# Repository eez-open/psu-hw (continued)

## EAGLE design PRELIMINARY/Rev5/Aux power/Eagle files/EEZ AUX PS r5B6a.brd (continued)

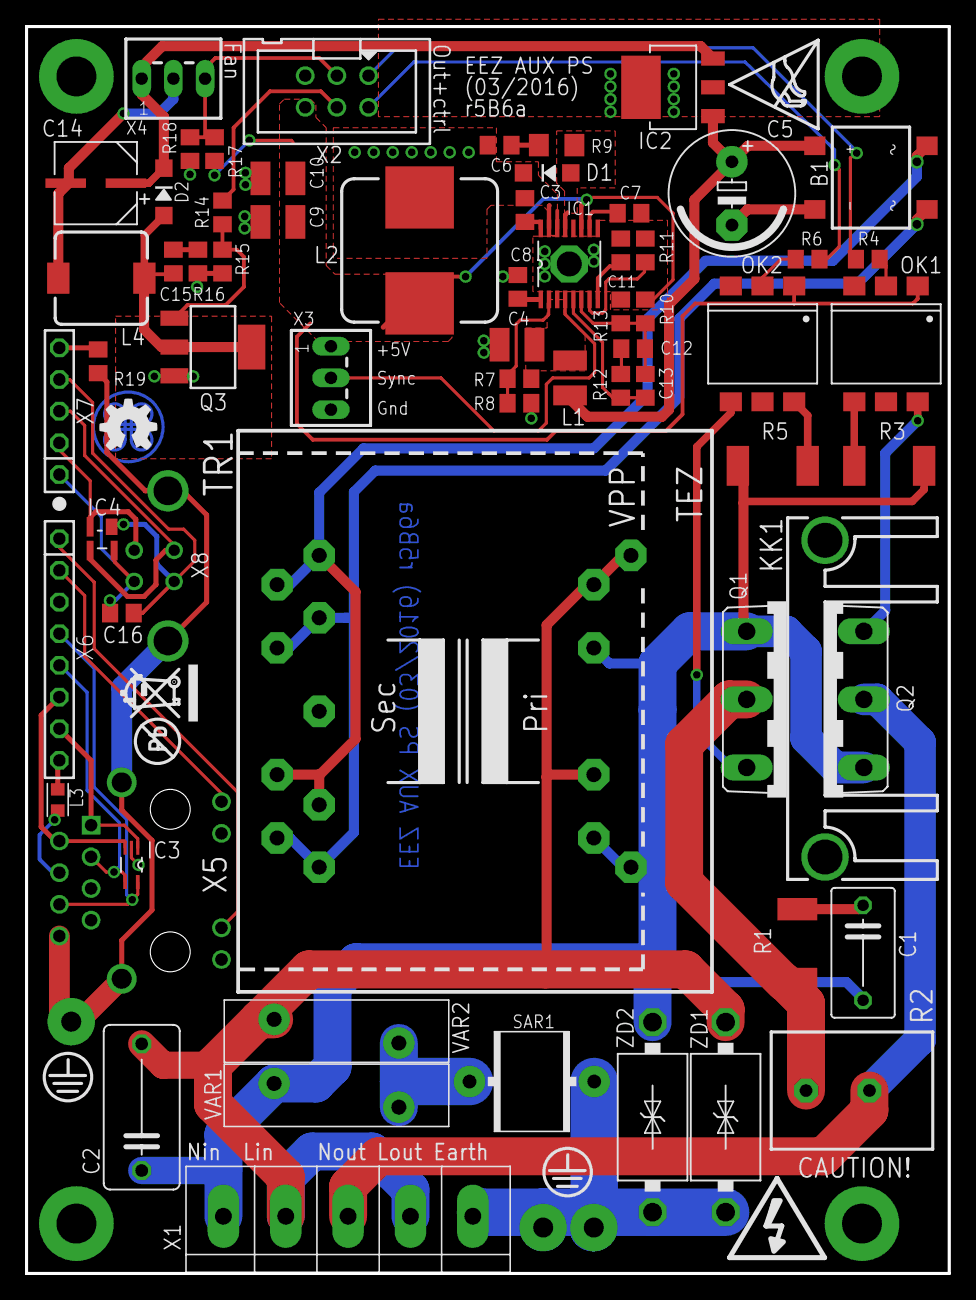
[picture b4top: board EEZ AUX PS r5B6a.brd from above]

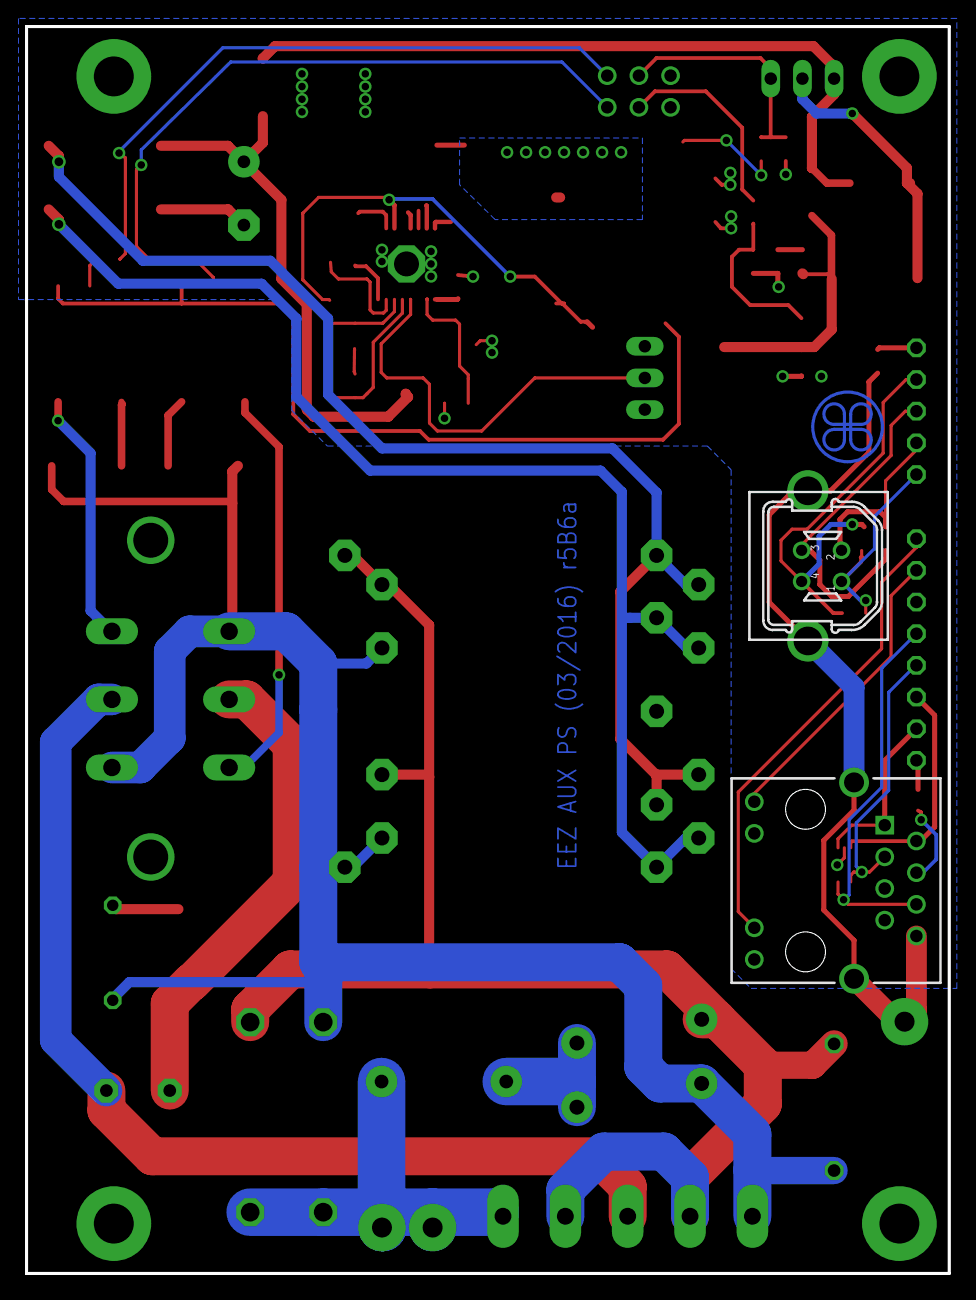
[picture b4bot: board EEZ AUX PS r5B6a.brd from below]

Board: 3 copper layers, 74.0 x 100.0 mm, 70 parts (2 on the bottom side), 54 nets.

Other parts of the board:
EEZ_SIGNATURE: SIGNATURESMALL; SIGNATURE_5MM
U$2: RECYCLE_BIN1/8
U$3: PB_SMALL
U$4: ESD_SYMBOL
